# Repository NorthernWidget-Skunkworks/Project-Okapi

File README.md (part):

# Okapi: Data logger with integrated solar charging and modular telemetry

***Okapi data logger (Resnik v0.4.0), with a micro-SD card for local storage and a Particle Boron telemetry module.***

The **Okapi** data logger responds to the need for a robust, flexible, and power-efficient open-source option to record and transmit data from remote locations. It is programmable using the open-source standard Arduino framework via a standard micro-USB cable and supports a wide range of sensor input/output options. It connects to dual power supplies to ensure consistent recordings, and interfaces with a range of “Feather”-form-factor boards for telemetry.

## Namesake

The Okapi, a relative of the giraffe, communicates over long distances using [infrasound](https://en.wikipedia.org/wiki/Infrasound). The telemetry capabilities of this data logger inspired this namesake.

## Technical specifications

### Electronic Hardware

* Microcontroller (computer) core
  * ATMega1284p
  * Arduino compatible
  * Programmable using C++
  * 8 MHz
* Real-time clock
  * DS3231M
  * Temperature-compensated crystal for high accuracy (±5 ppm)
* Sensor and general-purpose connections
  * Primary Rail (selectable 3.3V or 5V)
    * I2C (up to 128 sensors permitted; expansion ports provided by Project Heptapod)
    * SPI
    * 2x 16-bit analog
    * Analog voltage reference
    * 12-bit Digital-to-analog conversion
    * 2x General-purpose input/output
    * USART
    * 2x Vbus (selectable 3.3V or 5V)
    * 2x Ground
  * Secondary Rail (selectable 3.3V or 5V)
    * I2C (up to 128 sensors permitted; expansion ports provided by Project Heptapod)
    * 2x 16-bit analog
    * 2x General-purpose input/output
    * USART
    * 2x Vbus (selectable 3.3V or 5V)
    * 2x Ground
* Data storage and return
  * Local storage: micro SD card
  * Telemetry: support for Feather-profile boards, including Particle devices:
    * Mobile phone networks
    * WiFi
    * Bluetooth
    * [In development] Iridium satellite
* Power
  * Dual power supply
  * Primary Power
    * Built-in maximum-power-point-tracking solar-charge-control circuitry
    * Lithium-Ion battery
  * Backup Power
    * Alkaline AA batteries
  * Real-time clock
    * Coin cell
  * Power consumption
    * Primary power, sleeping: 80 μA
    * Backup power, sleeping: 4 μA
    * Active (typical: data logger without sensors): 10 mA
    * Transmitting (mobile networks, typical: Particle Boron):
      * 16 mA background
      * 40 mA burst
  * Power generation
  * Solar, low light: 100 mA
* User interface
  * “Log” button: instantaneous reading (for testing)
  * “Reset” button
  * 2x 3-color indicator LEDs
  * Computer readout via a serial monitor, included in the Arduino software
* Open-source licensing via CC BY-SA 4.0

>> @bschulz1701: Any updates needed? I think that there is also a WDT (correct?)

### Electronic Software and Firmware

* Programmable using the Arduino IDE https://www.arduino.cc/en/main/software
* Custom bootloader and board definition for ATMega1284p available via https://github.com/NorthernWidget/Arduino_Boards
* Custom libraries from Northern Widget and the open-source community
  * Primary data-logger functions
  * Libraries available with each sensor, exposing a standard interface
* Open-source licensing via GNU GPL 3.0

### Pinout and board interfaces

***Okapi data logger (Resnik v0.4.0) with pins, connectors, and interactive items annotated.***

**Pins are colored following this convention:**
* Ground: black
* Power supply: red
* Universal Serial Asynchronous Receiver--Transmitter (USART or UART): blue
* General-purpose I/O pins: gray
* Analog inputs and associated reference voltage: green
* Digital communications buses (SPI and I2C): purple
* Analog adjustable voltage output: salmon

**The power and programming connectors at the "south" end of the board are as follows:**
* Micro-USB connector
  * The same connector as many Android and other mobile phones at the time of writing; may be programmed using any USB cable for these that is not charging-only (i.e. that can carry data)
  * Can be used with our [clock-setting program](https://github.com/NorthernWidget/SetTime_GUI) to set the time on the real-time clock.
  * Provides power to the data logger while it is connected; this power source is isolated from the batteries and solar panel, and therefore may be plugged in safely at any time.
* Solar panel, 4.95--32.0 V. A wide range of panels can work with this.
* Li-Ion battery, 2.60--4.475 V. This works with standard 18650 Li-ion batteries. It can work well with just a single battery, but if more storage is required, multiple 18650 batteries may be connected in parallel; we have a circuit-board design to do this: https://github.com/NorthernWidget/LiIon-18650-Parallel. ***CAUTION***: most commercially available multiple-18650-battery holders connect them in series; this voltage is ***TOO HIGH*** for the data logger.
* Primary batteries. This is ideally a pack of 3 primary (i.e., not reusable) Alkaline (or better) AA batteries with a long shelf life. The Okapi data logger will switch to these if its rechargeable power supply shuts down. The internal electronics reduce the quiescent power consumption while under backup power (see the above list of [electronic hardware technical specifications](#electronic-hardware)) and inform the logger about which power supply is being used, allowing it to, for example, reduce or temporarily terminate data transmission.

>> @bschulz1701: Solar panel supply current / size?

**"RST" and "LOG" buttons:**
* Reset ("RST"): stop the program that is currently executing on the main logger and return it to its boot sequence.
* Log Now ("LOG"): take a reading immediately. This is useful for diagnoses and testing.

>> General note: we may want to have an LED flash whenever the logger takes a reading -- even for 1/10 of a second. With an option to disable this, of course. But it is often better to know while in the field that a system is working

**Other notes, clockwise from the top:**
* The socket holds a [Feather-form-factor board](https://learn.adafruit.com/adafruit-feather/feather-specification).
  * This standard, designed by [Adafruit](https://www.adafruit.com/), has been widely adopted, including by the IoT/telemetry module designer [Particle](https://www.particle.io/).
  * We often use a [Particle Boron mobile-phone telemetry unit](https://docs.particle.io/boron/).
* Mounting holes for [\#4 screws](https://www.mcmaster.com/91772A106/)
* CR1220 battery; can power the real-time clock for up to 7 years
* ISP header (also called an ICSP header): This 3x2 header is used with an in-system programmer (in-circuit system programmer) to upload the (bootloader)[#installing-the-bootloader] to the data logger.
* A micro-SD card holds a copy of all data, whether or not any telemetry is used

>> @bschulz1701: check my clock 7-year figure

***Okapi data logger (Resnik v0.4.0) with key microchips, LEDs, and switches marked.*** *MCU: Microcontroller. RTC: Real-time clock. LED: Light-emitting diode. Bus: a subsystem for connections and data transfer.*

The Okapi data logger contains two buses (see above), each of which has an independent voltage. The primary bus is on the left and the secondary bus is on the right. These can be selected as 3.3V (switches slid towards the inside of the board) or 5V (switches towards the outside of the board).

>> @bschulz1701: How much power can each bus source/sink?

Two LEDs, status and auxiliary, flash messages to the user to provide information on proper operations vs. a variety of possible errors. These are useful for field diagnoses, and are further described in [the field guide section, below](#field-guide).

>> Design note: move STAT label to left of LED so it can be better seen

The Li-ion override button, which can be pressed with the tip of a pen or other small object, ...

>> @bschulz1701: This somehow overrides the Li-Ion battery electronics to allow something to happen... but I am not remembering what!

## On-board Devices

### I2C

| **Device**                                                        	| **Default address** 	| **Reprogrammable address** 	| **Function**                                                     	|
|-------------------------------------------------------------------	|---------------------	|----------------------------	|------------------------------------------------------------------	|
| [DS3231](https://github.com/NorthernWidget/DS3231_Logger)         	| 0x68                	| N                          	| Real-time clock                                                  	|
| [MCP23018](https://github.com/NorthernWidget-Skunkworks/MCP23018) 	| 0x20                	| N                          	| I/O Expander                                                     	|
| [ADS1115](https://github.com/adafruit/Adafruit_ADS1X15)           	| 0x48                	| N                          	| ADC (on-board devices)                                           	|
| [ADS1115](https://github.com/adafruit/Adafruit_ADS1X15)           	| 0x49                	| N                          	| ADC (off-board devices)                                          	|
| [MCP4725](https://github.com/NorthernWidget-Skunkworks/MCP4725)   	| 0x62                	| N                          	| DAC                                                              	|
| [BME280](https://github.com/NorthernWidget/BME_Library)           	| 0x77                	| N                          	| On-board barometric pressure, temperature, and relative humidity 	|

### SPI

* SD Card

### UART (USART)

* FTDI USB-Serial converter
* Feather form-factor telemetry board; typically [Particle Boron](https://docs.particle.io/boron/)

## Assembly

Assembling this data logger is possible by hand with sufficient skill and the following tools:
* Temperature-controlled soldering iron
* Hot-air rework station
* Equipment for stenciling with solder paste
* ESD-safe tweezers and workstation
* Solder wick

Mechanized assembly by a professional circuit-board assembly house, which is available in many parts of the world, may be preferred due to the complexity of this data logger board.

>> THOUGHT: I have basic instructions for assembly on the [Project Walrus](https://github.com/NorthernWidget-Skunkworks/Project-TPDH-Walrus) README; I will not reproduce these here just yet, as we might want to set up a separate assembly guide, mostly with good links to existing resources, since our writing something of this nature would be to reinvent the wheel.

## Programming

### Downloading and installing the Arduino IDE

Go to https://www.arduino.cc/en/main/software. Choose the proper IDE version for your computer. For Windows, we suggest the non-app version to have more control over Arduino; this might change in the future. You will have to add custom libraries, so the web version will not work (at least, as of the time of writing). Download and install the Arduino IDE. Open it to begin the next steps.

### Installing the bootloader

Before a data logger can receive programs via the convenient USB port, it must have a *bootloader* that tells it to expect to receive new programs that way.  You can read more about bootloaders in general here: https://www.arduino.cc/en/Hacking/Bootloader.

Because you can't upload the bootloader via USB, you use the 2x3-pin 6-pin ICSP (also called ISP) header with a special device called an "in-circuit system programmer" (or just "in-system programmer; yup, that's what the acronym stands for).

Many devices exist to upload a bootloader including:
* The official [AVR ISP mkII](http://ww1.microchip.com/downloads/en/DeviceDoc/Atmel-42093-AVR-ISP-mkII_UserGuide.pdf) (no longer produced but available used)
* Using an [Arduino as an ISP](https://www.arduino.cc/en/tutorial/arduinoISP)
* The versatile [Olimex AVR-ISP-MK2](https://www.olimex.com/Products/AVR/Programmers/AVR-ISP-MK2/open-source-hardware)
* The [Adafruit USBtinyISP](https://www.adafruit.com/product/46)

To upload the bootloader, do the following:

1. Open the Arduino IDE. If you have not yet installed the Northern Widget board definitions, find and install them here (instructions provided): https://github.com/NorthernWidget/Arduino_Boards
2. Select the desired board -- most likely ***ATMega1284p 8MHz*** under *Northern Widget Boards*.
3. Plug the data logger into your computer via a micro-USB cable to provide power.
4. Plug your ISP of choice into your computer (via a USB cable) and onto the 6-pin header. There are two ways to place it on; the header is aligned such that the ribbon cable should be facing away from the board while programming. If this fails without being able to upload, try flipping the header around.
5. Go to Tools --> Programmer and select the appropriate programmer based on what you are using.
6. Go to Tools --> Burn bootloader. Typically, within a few seconds, you learn whether you succeeded or failed. Hopefully it worked!

***Important note for Linux users:*** You must supply permissions to the Arduino IDE for it to be able to use the ICSP, or you will have to run it using `sudo`. The former option is better; the latter is easier in the moment.

***Note: Be sure to download and/or update drivers for your ISP.***

### Installing the requisite software libraries

>> @awickert: Add a full list of the requisite software to install; finish the firmware aggregator and use those directions (or the Arduino ones) to help users install that + sdfat. Include screenshots and host those directions at https://github.com/NorthernWidget-Skunkworks/Firmware-Aggregator.

### How to write a program

The below program is an example that you can copy and paste directly into the Arduino IDE in order to upload to your data logger. We'll walk you through what each piece of the code is and does.

#### Full program
```c++
/*
 * Okapi example: connected with a Walrus pressure--temperature sensor, often
 * used for water-level measurements, via the Longbow I2C/RS-485 translator.
 * Written by Bobby Schulz with a few comments added by Andy Wickert.
 */

#include "Okapi.h"
#include <TP_Downhole_Longbow.h>

TP_Downhole_Longbow Walrus; // Instantiate Walrus sensor; relict library name
Okapi Logger; // Instantiate data logger object

String Header = ""; // Information header; starts as an empty string
uint8_t I2CVals[1] = {0x22}; // I2C addresses of sensors

unsigned long UpdateRate = 60; // Number of seconds between readings

void setup() {
  Header = Header + Walrus.GetHeader();
  Logger.begin(I2CVals, sizeof(I2CVals), Header); // Pass header info to logger
  Init();
}

void loop() {
  Logger.run(Update, UpdateRate);
}

String Update()
{
  Init();
  delay(1500);
  return Walrus.GetString();
}

void Init()
{
  Walrus.begin(13, 0x22); // Instantiate Walrus (at address = 13)
                          // and Longbow Widget (at address = 0x22)
}
```

#### "Include" statements

```c++
#include "Okapi.h"
#include <TP_Downhole_Longbow.h>
```

These bring in the two code libraries involved, the former for the data logger and the latter for the sensors. This allows the user to access the classes and functions within these two libraries, as we will show in more detail below.

#### Instantiate a sensor object

```c++
TP_Downhole_Longbow Walrus; // Instantiate Walrus sensor; relict library name
Okapi Logger; // Instantiate data logger object
```

"Instantiating an object" means that we create our own specific versions of the a class of items. This can be thought of as: `Breakfast myBreakfast`. Breakfast is the general concept, but I create "myBreakfast", which I can then modify. In this same way, "Logger" is what we call our Okapi data logger, and "Walrus" is what we call our "TP_Downhole_Longbow" sensor; this name is a holdover from an earlier design that is the ancestor of the Walrus. We can then access functions and variables within these two instantiated objects.

#### Declare the header string

```c++
String Header = ""; // Information header; starts as an empty string
```

We start with an empty header, but will soon add information to it.

#### Create a list of the I2C addresses of the sensors

```c++
uint8_t I2CVals[1] = {0x22}; // I2C addresses of sensors
```

This is the trickiest step. You need to know what the I2C address of your sensor is. You can skip this, but then the logger will not run a check to see if the sensor is properly connected.

>> Let's make sure that we record this one each page, or find a way to replace this.

#### Declare the amount of time between logging events

```c++
unsigned long UpdateRate = 60; // Number of seconds between readings
```

This is the number of seconds between logging events. If it takes 2 seconds to record data, make sure that you give the logger at least 3 seconds between events. The maximum logging time is set by the watchdog timer, which [FINISH HERE]

>> @BSCHULZ1701: Is there an external WDT on Okapi?

#### `setup()` step: runs once at the start

```c++
void setup() {
  Header = Header + Walrus.GetHeader();
  Logger.begin(I2CVals, sizeof(I2CVals), Header); //Pass header info to logger
  Init();
}
```

`setup()` is a special function that runs just once when the logger boots up. In this case, it first adds the Walrus' header to the header string. `GetHeader()` is a standard function that lies within each of our sensor libraries and returns this header information as a `String`. We then pass the header and the I2C values to the Okapi library's `begin()` function. This sets up the header and prepares the data loger to record data. Finally, this function calls `Init()`, which we skip ahead to describe immediately below.

>> (awickert): I still don't understand why we have to pass `sizeof()` and can't just compute that within the function.

#### `Init()` function: skipping ahead to understand `setup()`

```c++
void Init()
{
  Walrus.begin(13, 0x22); // Instantiate Walrus (at address = 13)
                          // and Longbow Widget (at address = 0x22)
}
```

The `Init()` function calls the `begin()` function, standard within each Northern Widget sensor library, to instantiate the connection ports (e.g., I2C, RS-485) used to communicate between the sensor and the logger. In this case, there is only one sensor, but two ports are needed: An RS-485 signal goes from the Walrus to the Longbow Widget, which then converts the signal into an I2C signal with its own address. The reason for this is that an I2C signal can travel only ~3 m, but an RS-485 signal can travel ~100 m.

#### `loop()` step: keeps running until stopped

```c++
void loop() {
  Logger.run(Update, UpdateRate);
}
```

The loop calls the main function of the Okapi library, `run()`, repeatedly. This puts the logger into a low-power sleep mode and wakes it up only when interrupted by the clock or the "LOG" button. `Update` refers to the function described immediately below. `UpdateRate` is our logging interval defined above.

#### `Update()` function: Gives data for the logger to record

```c++
String Update()
{
  Init();
  delay(1500);
  return Walrus.GetString();
}
```

The `Update()` function first calls the `Init()` function to be sure that the sensor is ready to log. It then in this case delays 1500 milliseconds; this is an ad-hoc solution to the question of how long it takes the pressure transducer to settle after being started up, and is a safe large amount of time. This function then can `return` a string of all of the Walrus' readings (one pressure and two temperature measurements) separated by commas. This is then concatenated to a list of logger-internal measurements -- date/time; on-board temperature, pressure, and relative humidity; and onboard voltages for battery and solar-panel status -- and recorded to the SD card. If telemetry were present, these data could also be sent to a remote location.

### Reference

A full index of the public variables and functions within the Okapi data logger library is available at https://github.com/NorthernWidget/Okapi_Library.

>> Send user to library page

>> Thoughts: We should make all comments compatible with doxygen (following) what I did with the ALog library. It also looks like TravisCI has support for Arduino(!) This means that we could also automate construction of the documentation for these libraries.

### Integration with Particle Boron

>> @bschulz1701?

## Wiring

>> Example needed

## Power supply

* **Lithium-ion 18650 rechargeable batteries**; this board can hold two in parallel: https://github.com/NorthernWidget/LiIon-18650-Parallel
* **Solar panel**. A wide range is acceptable, but we like [Voltaic Systems' 6-watt panel](https://voltaicsystems.com/6-watt-panel/). If you do not want to snip off the barrel jack, [this extension plug from Adafruit should work](https://www.adafruit.com/product/2788) (though we have not tested it... and you'll also have to cut *it* in half).
* **Primary alkaline batteries**; we typically use three high-quality (e.g., Duracell) AAs. These are the backup power supply, and we place them in a [3xAA holder (in series for the proper voltage) with a switch](https://www.jameco.com/z/SBH-331-AS-R-3x-AA-Battery-Holder-with-Cover-and-Switch_216144.html).

>> @bschulz1701: new smarter 18650 holder?

## Housing

The below suggestions encompass what we use and suggest for the housing. In the end, any sufficiently waterproof enclosure will work.

### Materials

* **Enclosure**: [PolyCase WH-16-03 outdoor-rated hinged enclosure](https://www.polycase.com/wh-16)
* **Cable glands**: [RDC07AA](https://www.elecdirect.com/catalogsearch/result/?q=RDC07AA). One per sensor, plus one for the solar panel.
>> AW: Photo didn't take; look up
* **Fasteners**
  * [M5-0.8 x 10 mm truss head screws](https://www.mcmaster.com/92467A320/) x4 to attach mounting plate to threaded inserts in the enclosure
  * [\#4-40 x 1/4 in pan head screws](https://www.mcmaster.com/91772A106/) x22 to attach Okapi, battery packs, and mounting plate to standoffs
  * [\#4-40 x 2 in Female Threaded Hex Standoffs](https://www.mcmaster.com/91115A173/) x3 to stand off Okapi from mounting plate
  * [\#4-40 x 1/2 in Female Threaded Hex Standoffs](https://www.mcmaster.com/91920A533/) x8 to stand off AA battery pack and Li-Ion battery pack from mounting plate
* **Mounting plate for Okapi** (Milled, ABS)
  * [Mounting Plate Design](Mounting%20Plate)
* **Power**
>> Solar panel
  * [3x AA battery pack BK-1280-PC6](https://www.digikey.com/en/products/detail/mpd-memory-protection-devices/BK-1280-PC6/1640076) for alkaline battery backup, mounting holes included for #4-40 screws
>> Li-Ion battery and holder

### Tools

* CNC mill and/or drill press
* Deburring tool or knife + skill and patience
* Torque wrench(es) for 1.0, 1.2 N m

### Assembly

>> Guide with photos. Perhaps ask @superchap123 to use his CNC

>> Placeholder for Now

>> Also include information on passing wiring through

## Field operator's guide

### Initialize
1. Ensure that all connections are secure and SD card is inserted
2. Turn battery pack on
3. Wait for GREEN - GREEN - 5x Blue Flash
	- If you see this, the logger is properly recording data. To double-check, go to "Check"
	- If you see a different flash pattern, go to "Error"

### Check
1. After going through "Initialize", wait 2-3 minutes
2. Follow the instructions in the "Download" section
3. Check to make sure that all the data are being recorded at the proper (UTC) time
4. Check that valid values are being recorded for sensors
7. Whether or not files are properly recorded, return to "Initialize"
	- If files are not recorded, replace the SD card, check all connections, turn the logger back
	  on, and try again
	- If there is an issue with a specific sensor, check connections and troubleshoot
	- If files are recorded properly, return to Initilaize and do not return to "Check"

### SD card swap
1. Turn battery pack off
2. Remove SD card. Ensure that it is labeled. Put it somewhere safe and memorable
3. Replace the SD card with an equivalently labeled SD card
4. Go to "Initialize"

### Download
1. Turn battery pack off
2. Remove SD card
3. Insert SD card in computer
4. Navigate in the SD card to the most recent "log" file (NW→<serial_number>→Log<number>.txt)
5. Save the data file in a well-labeled and organized place.
6. Safely eject the SD card from the computer
7. Go to "Initialize"

### Error

#### Status Codes

The first LED (AUX) will turn green so long as power is applied.
The second LED (STAT) will have one of the colors below.

**Green:**: All systems check out OK, logging will proceed

**Orange:**: A sensor system is not registering properly, some sensor data may be missing or incorrect
* Verify correct polarity of sensor connection
* Ensure the right sensor is connected
* Verify the screw terminals are well connected to the wires (a loose connection can cause a failure)
* Make sure battery power is applied, some sensors can fail otherwise

**Cyan:**: Clock time is incorrect, but logger is otherwise working correctly
* Connect the logger to a computer and reset the clock using the Northern Widget Time Set GUI
* Start Processing
* Open the Northern Widget Time Set program
* Note and record the wrong time if the logger has been out in the field, alongside the current (correct) time, to correct the prior measurements
* Click the "set time" button and check that you are <3 seconds off of the correct time
* Click the "close" button

**Pink**: (looks like purple to some people): SD card is not inserted
* Insert the SD card, or remove and re-insert to make sure card is fully seated

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
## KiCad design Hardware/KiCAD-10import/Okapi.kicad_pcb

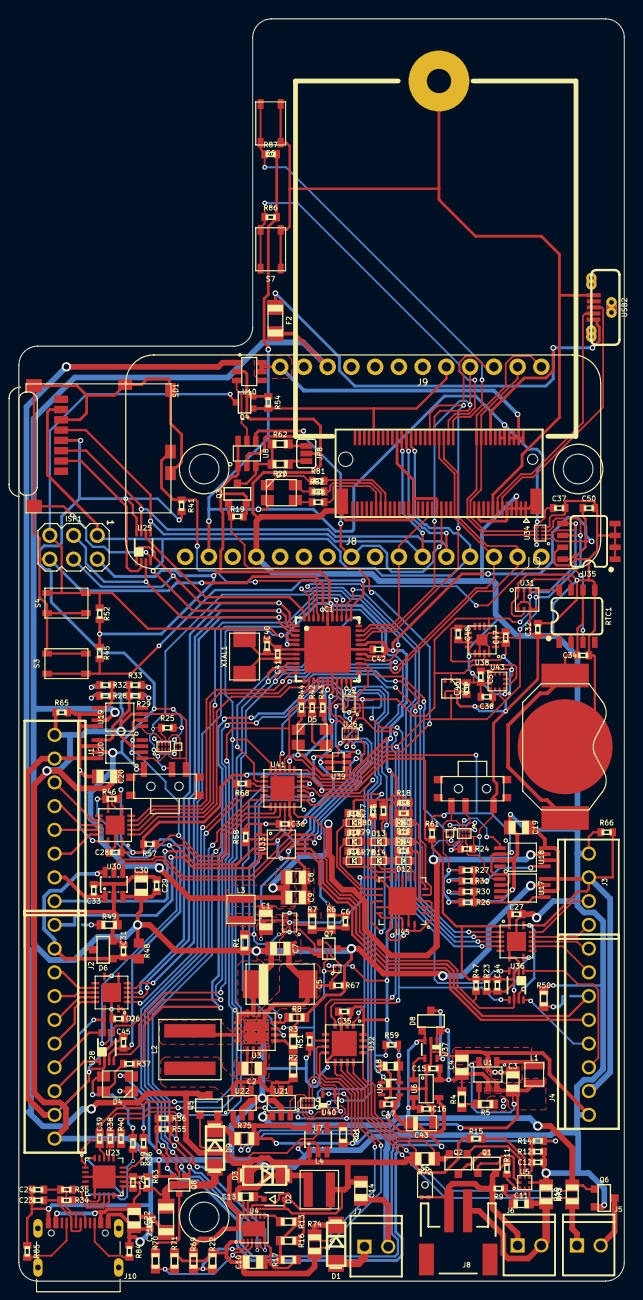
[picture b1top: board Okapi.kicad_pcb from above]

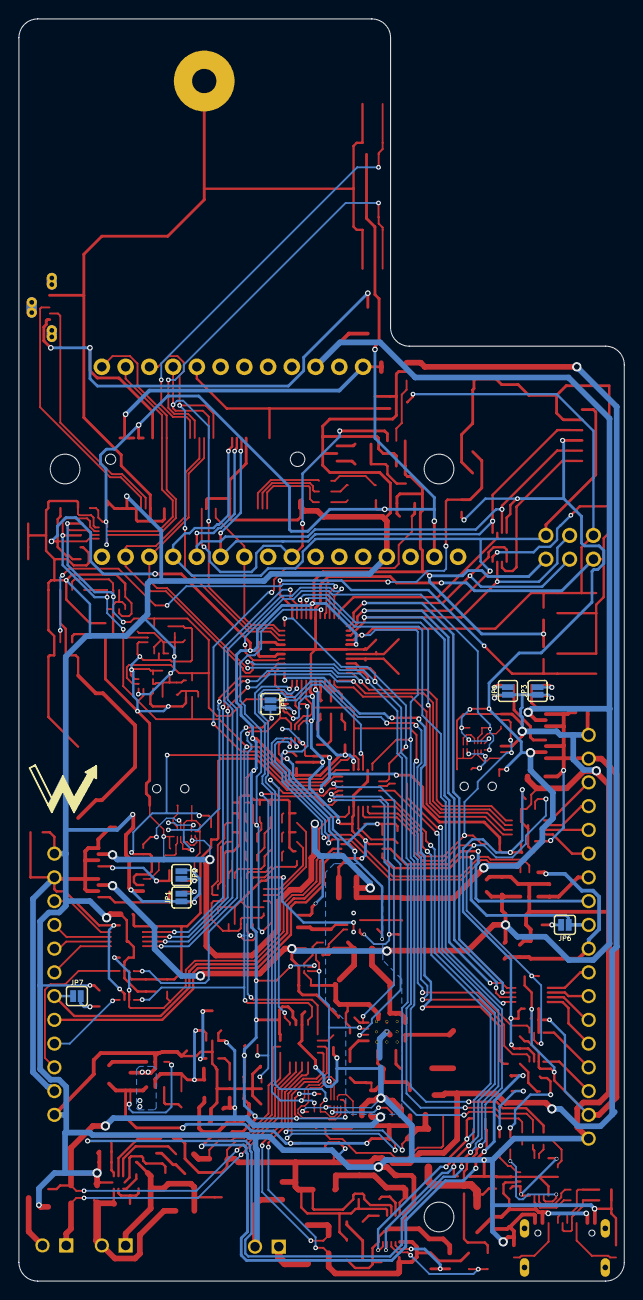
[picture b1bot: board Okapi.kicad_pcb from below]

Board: 2 copper layers, 64.8 x 135.0 mm, 252 parts (8 on the bottom side), 207 nets.

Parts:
BT1: BATTERY_COIN12MM; LINX_BAT-HLD-012-SMT
C1: 4.7uF; C0805
C2, C7, C8, C9, C10, C19, C20: 22uF; C0805
C3, C4, C14, C22, C30: 10uF; C0805
C5: 220uF; C2917
C6: 68pF; C0402
C11, C13: 1uF; C0603
C12, C17, C21, C25, C26, C27, C28, C29, C31, C32, C33, C34, C35, C36, C37, C38, C39, C44, C45, C46, C47, C48, C50, C57: 0.1uF; C0402
C15, C16: 0.22uF; C0402
C18: 4.7uF; C0603
C23, C24, C40, C41: 12pF; C0402
C42: 1uF; C0402
C43: 100uF; C1206_TANT
D1, D3, D9: DO214AC
D2: SOD323-R
D4, D5, D7: CLVBA-FKA
D6: SOT23-3
D8: BAT54C; SOT23-3@1
D10, D13, D16: LEDGREEN0603; LED_0603
D11, D14, D17: LEDYELLOW0603; LED_0603
D12, D18: LEDRED0603; LED_0603
F1, F2: 1206
H1, H2, H3: 4_40
IC1: ATMEGA1284M; MLF44-TH
ISP1: AVRISP-6; AVRISP
J1, J4: CONN_82.54_SCREW; 1X08_SCREW
J2: 1X10_SCREW
J3: CONN_42.54_SCREW; 1X04_SCREW
J5, J6, J7: 1X02_2.54_SCREWTERM
J8: JST-2-SMD
J9: B_SERIES_M.2EKEY_NOPROG; PARTICLE_M.2EKEY_NOPROG
J10: USB_C_CUSB31-CFM2AX-01-X
JP1, JP2, JP3, JP4, JP5, JP6, JP7: JUMPER-SMT_2_NO_SILK; SMT-JUMPER_2_NO_SILK_528
JP8: JUMPER-SMT_3_1-NC_PASTE_SILK; SMT-JUMPER_3_1-NC_PASTE_SILK_528
L1: 6.8uH; 1008
L2: 10uH; WE-XHMI(6.65X6.45)
L3: 1uH; WE-LQS(3X3)
L4: 4.7uH; WE-MAIA(4.1X4.1)
MS1: FEATHERWINGLAYOUT; FEATHERWING_MIN
Q1, Q2, Q6: DMG3404; SOT23-3
Q3, Q5: FDN360P; SOT23-3@1
Q4, Q7, Q8: 2N7002; SOT323
R1, R5, R7, R8: 180k; R0603
R2, R4: 1.62M; R0603
R3: 360k; R0603
R6: 820k; R0603
R9, R36, R37, R38, R39, R40, R42, R43, R44: 330; R0402
R10: 3m; R0805
R11: 20; R0402
R12: 1k; R0402
R13: 182k; R0603
R14: 100R; R0402
R15: 2k; R0402
R16: 91k; R0603
R17, R62: 330k; R0603
R18, R23, R57, R58, R61, R63: 100k; R0402
R19: 120k; R0402
R20: 130k; R0603
R21: 470k; R0603
R22: 143k; R0603
R24, R25, R41, R45, R46, R47, R52, R67: 10k; R0402
R26, R27, R28, R29, R30, R31, R32, R33: 287R; R0402
R34, R35: 27; R0402
R48: 330R; R0603
R49, R50: 10k; R0603
R51, R54, R84, R85, R86, R87: R0402
R53, R60, R64, R76, R77, R78, R79, R80: 220R; R0402
R55, R56, R59, R68: 1M; R0402
R65, R66: 180k; R0402
R69: 100k; R0603
R70: 200k; R0603
R71: 1M; R0603
R72, R73, R74, R75: R0805
R81, R82, R83: 5.6k; R0402
RTC1: DS3231M; SO08
S1, S2: SPDTPCM12; PCM12
S3, S4, S6, S7: BUTTON4.2X3.2; SWITCH_4.2X3.2
S5: BUTTON2.6X1.6; SWITCH_2.6X1.6
SD1: MICROSDCD; MICROSD_CD
U1: TLV61220DBV; DBV_R-PDSO-G6
U2: TPS62822DLC; DLC_8
U3: TPS61032RSA; RSA_S-PVQFN-N16
U4: DFN_12_3X3
U5: BQ2980RUG; RUG_S-PQFP-N8
U6: TPS2105; SOT23-5
U7: LTC4412S6; SOT23-6L
U8: TPL5111DDC; DDC_R-PDSO-G6
U9: TPS79733; DCK_R-PDSO-G5
U10, U21, U22: TPS22917DBV; DBV_R-PDSO-G6
U11, U12, U13: SN74AUP1G04YFP; DSBGD_4
U14, U15, U16: SN74AUP2G08DQE; DQE_R-PX2SON-N8
U17, U18, U19, U20: MIC2544MSOP; MSOP_8
U23: FT231X-Q; QFN20
U24: SN74LVC1G3157DRL; DRL_R-PDSO-N6
U25: SN74AUP3G34DCU; DCU_(R-PDSO-G8)
U26, U34: TXS0102DQM; DQM_R-PX2SON-N8
U27, U29, U42: TXS0104RGY; RGY_S-PVQFN-N14
U28, U36: TCA9406DCU; DCU_(R-PDSO-G8)
U30: MCP4726A2SOT-23; SOT23-6L
U31: BME280
U32: PAC1934QFN; QFN16
U33: ADS1115; VSSOP_10
U35: MB85RC; SO08
U37: TLV3691DCK; DCK_R-PDSO-G5
U38: MLX90393; QFN16_3X3
U39: MIC94094C6; SC-70_6
U40: SN74AHC1G86DCK; DCK_R-PDSO-G5
U41: MCP23018QFN; QFN24
U43: BMA456; LGA-12_2X2
U44: VEML6030
U45: PCA9634QFN; QFN20_5X5
U$1, U$2: VDIV-JP; VDIV_GENERIC
U$4: NWLOGO_MED
USB2: USB_MICROVERT; USB_MICRO_VERT_MOLEX
XTAL1: CRYSTAL8MHZ5X3.2; CRYSTAL_5X3.2_2-SMD

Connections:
3V3_AUX: C6.1, C8.1, C9.1, C32.1, C38.1, C46.1, C47.1, C48.1, C57.1, L3.P$2, R6.2, R24.2, R25.2, R41.2, RTC1.2, S1.1, S2.1, SD1.4, U11.A2, U12.A2, U14.8, U15.8, U18.7, U20.7, U24.5, U25.8, U31.2, U31.5, U31.6, U31.8, U38.2, U38.8, U38.15, U39.6, U43.3, U43.7, U43.10, U44.4, U44.6
3V3_AUX_PG: R1.1, U2.8, U41.2
3V3_CORE: C18.1, C35.1, C42.1, C50.1, D4.2, D5.2, IC1.5, IC1.17, IC1.27, IC1.29, IC1.38, ISP1.2, Q3.2, R18.2, R19.2, R45.2, R52.2, R53.2, R55.2, R56.2, R59.2, R60.2, R64.2, R76.2, R77.2, R78.2, R79.2, R80.2, U8.1, U8.6, U9.5, U13.A2, U16.8, U32.2, U32.15, U32.16, U34.1, U35.8, U39.4, U40.5, U41.8, U45.3, U45.15, U45.18, U45.20
3V3_CORE_ISO: C26.1, C27.1, C28.1, C44.1, C45.1, R23.2, R46.2, R47.2, R57.2, R61.2, U26.1, U26.5, U27.1, U28.3, U29.1, U36.3, U39.1, U42.1
3V3_FEATHER: C37.1, D7.2, J9.10, J9.12, MS1.2, R86.2, R87.2, U34.5, U34.8
3V3_FTDI: C25.1, U23.10, U23.11, U23.20
5V_AUX: C1.1, C5.+, C7.1, C29.1, C30.1, C36.1, F2.2, MS1.26, Q7.3, R1.2, R8.2, R48.2, R58.2, R67.2, U2.7, U3.1, U3.15, U3.16, U17.7, U19.7, U26.8, U30.3, U33.1, U33.8
5V_LP: C4.1, C15.1, D8.2, R4.2, U1.5, U6.5, U37.1
ADC_0: J1.8, U33.4
ADC_1: J2.1, JP6.1, U33.5
ADC_2: J4.5, U33.6
ADC_3: J4.6, JP7.1, U33.7
ADC_EXT_ALERT: R58.1, U33.2, U41.22
ALIVE_LED: IC1.23, R37.2
BLUE: J9.65, R83.2
BMS_CTR: R14.1, U41.16
BSOM_VUSB: F2.1, J9.16, USB2.1
BUS_LOGIC_EN_PRIME: R46.1, U27.8, U28.6, U29.8, U41.21
BUS_LOGIC_EN_SEC: R47.1, U36.6, U41.24, U42.8
C0: IC1.21, U16.2, U40.1
C1: IC1.22, U16.6, U40.2
CC1: J10.A5, R85.2
CC2: J10.B5, R84.2
CSA_~ALERT: U32.1, U41.4
CS_EXT: IC1.37, U27.2
CS_OUT: J2.6, U27.13
D+: C24.2, J10.A6, J10.B6, R35.2
D-: C23.2, J10.A7, J10.B7, R34.2
DAC_OUT: C33.1, J1.7, U30.1
DTR: C39.1, U23.18
EN_BUS_PRIME: IC1.26, R25.1, U15.1, U15.6
EN_BUS_SEC: IC1.25, R24.1, U14.1, U14.6
FAULT_PRIME: R57.1, U19.2, U20.2, U41.20
FAULT_SEC: R61.1, U17.2, U18.2, U41.6
FEATHER_BAT: J9.2, J9.4, J9.6, J9.8, MS1.28, U10.5, U10.6
FEATHER_CTS: IC1.31, J9.40, MS1.20
FEATHER_EN: Q3.1, R19.1, U41.7
FEATHER_GPIO: IC1.32, J9.43, MS1.10
FEATHER_RTS: IC1.30, J9.42, MS1.19
GLOBAL_INT: IC1.33, U41.14
GND: BT1.GND, C1.2, C2.2, C3.2, C4.2, C5.-, C7.2, C8.2, C9.2, C10.2, C12.2, C14.2, C15.2, C16.2, C17.2, C18.2, C19.2, C20.2, C21.2, C22.2, C23.1, C24.1, C25.2, C26.2, C27.2, C28.2, C29.2, C30.2, C31.2, C32.2, C33.2, C34.2, C35.2, C36.2, C37.2, C38.2, C40.1, C41.1, C42.2, C43.-, C44.2, C45.2, C46.2, C47.2, C48.2, C50.2, C57.2, D3.A, D6.2, IC1.6, IC1.18, IC1.28, IC1.39, IC1.TH, ISP1.6, J1.1, J2.10, J3.1, J4.1, J7.P1, J9.1, J9.3, J9.5, J9.7, J9.9, J9.15, J9.21, J9.39, J9.49, J9.56, J9.76, J9.77, J9.GND, J10.A1B12, J10.B1A12, JP1.1, JP2.1, JP3.1, JP4.1, JP8.2, MS1.4, Q4.2, Q6.2, Q7.2, Q8.2, R3.1, R5.1, R7.1, R10.2, R12.1, R17.2, R23.1, R26.1, R27.2, R28.1, R29.2, R49.1, R50.1, R51.1, R54.1, R63.1, R65.1, R66.1, R67.1, R69.1, R84.1, R85.1, RTC1.5, S1.3, S2.3, S3.1, S3.2, S4.1, S4.2, S6.3, S6.4, S7.3, S7.4, SD1.6, SD1.CD2, SD1.MT1, SD1.MT2, SD1.MT3, SD1.MT4, U1.2, U2.3, U2.5, U3.5, U3.6, U3.7, U3.13, U3.PAD, U3.PAD@1, U3.PAD@2, U3.PAD@3, U3.PAD@4, U3.PAD@5, U3.PAD@6, U3.PAD@7, U3.PAD@8, U3.PAD@9, U4.6, U4.EP, U5.4, U6.2, U7.2, U7.3, U8.2, U9.2, U10.2, U11.B1, U12.B1, U13.B1, U14.4, U15.4, U16.4, U17.3, U18.3, U19.3, U20.3, U21.2, U22.2, U23.3, U23.6, U23.13, U23.EP, U24.2, U25.4, U26.4, U27.7, U27.EP, U28.2, U29.7, U29.EP, U30.2, U31.1, U31.7, U32.3, U32.EP, U33.3, U34.4, U35.1, U35.2, U35.3, U35.4, U35.7, U36.2, U37.2, U38.4, U38.9, U38.10, U38.11, U38.12, U38.13, U38.14, U38.16, U38.EP, U39.2, U39.5, U40.3, U41.11, U41.23, U41.EP, U42.7, U42.EP, U43.1, U43.8, U43.9, U44.1, U45.1, U45.2, U45.8, U45.14, U45.19, U45.EP, USB2.5
GPIO_0: IC1.13, U29.2
GPIO_0_OUT: J1.6, U29.13
GPIO_1: IC1.36, U29.3
GPIO_1_OUT: J1.5, U29.12
GPIO_2: IC1.43, U42.5
GPIO_2_OUT: J4.7, U42.10
GPIO_3: IC1.35, U42.4
GPIO_3_OUT: J4.8, U42.11
GREEN: J9.63, R82.2
LBI: R8.1, U3.12, U41.3
LED1: IC1.14, R44.1
LED2: IC1.15, R42.1
LED3: IC1.16, R43.1
LI+: J6.P2, J8.2, Q1.2, R9.2, R11.2, S5.A, S5.A'
LI-: C11.2, J6.P1, J8.1, R10.1, U5.3
LOG_INT: IC1.34, R45.1, S3.3, S3.4
MISO: IC1.2, ISP1.1, J9.50, MS1.13, SD1.7, U27.3
MISO_OUT: J2.5, U27.12
MOSI: IC1.1, ISP1.4, U25.1, U27.4
MOSI_BUF: J9.52, MS1.12, SD1.3, U25.7
MOSI_OUT: J2.4, U27.11
MPPT_CHRG: Q8.1, R55.1, U4.4, U41.18
MPPT_FAULT: R56.1, U4.5, U41.19
MPPT_SHDN: R70.2, R71.1, U4.3
MPPT_VIN_REG: R22.1, R69.2, U4.2
unnamed: L3.P$1, U2.6
unnamed: C6.2, R6.1, R7.2, U2.2
unnamed: R2.1, R3.2, U3.9
unnamed: L2.2, U3.3, U3.4
unnamed: Q1.3, Q2.3
unnamed: R4.1, R5.2, U1.4
unnamed: Q1.1, U5.8
unnamed: L1.2, U1.1
unnamed: Q2.1, U5.7
unnamed: R15.2, U5.6
unnamed: R13.1, R16.2, R17.1
unnamed: C12.1, R12.2, R14.2, U5.5
unnamed: R11.1, U5.1
unnamed: R13.2, U4.7
unnamed: C11.1, R9.1, U5.2
unnamed: R68.1, U41.15
unnamed: C13.2, D2.C, U4.11
unnamed: JP8.3, R20.1
unnamed: C13.1, D3.C, L4.P$1, U4.12
unnamed: R51.2, U32.6
unnamed: Q8.3, R70.1
unnamed: U16.7, U21.3
unnamed: U16.3, U22.3
unnamed: D10.CATHODE, U45.4
unnamed: U12.B2, U15.5
unnamed: R28.2, R32.2, U19.5
unnamed: S2.2, U12.A1, U15.2
unnamed: U15.7, U19.1
unnamed: U15.3, U20.1
unnamed: JP3.2, R32.1
unnamed: JP4.2, R33.2
unnamed: R29.1, R33.1, U20.5
unnamed: U11.B2, U14.5
unnamed: S1.2, U11.A1, U14.2
unnamed: U14.7, U17.1
unnamed: U14.3, U18.1
unnamed: R26.2, R30.2, U17.5
unnamed: JP1.2, R30.1
unnamed: JP2.2, R31.2
unnamed: R27.1, R31.1, U18.5
unnamed: JP8.1, R62.1
unnamed: BT1.POWER0, BT1.POWER1, C34.1, RTC1.6
unnamed: R38.2, U23.17
unnamed: Q5.1, U7.5
unnamed: R21.1, U7.4
unnamed: R40.2, U23.1
unnamed: R35.1, U23.8
unnamed: R39.2, U23.14
unnamed: R34.1, U23.9
unnamed: D4.1, R39.1
unnamed: D4.3, R36.1
unnamed: D4.4, R37.1
unnamed: R36.2, U23.7
unnamed: D5.3, R42.2
unnamed: D5.4, R43.2
unnamed: D5.1, R44.2
unnamed: C40.2, IC1.7, XTAL1.OSC2
unnamed: C41.2, IC1.8, XTAL1.OSC1
unnamed: Q3.3, R20.2, R62.2, U8.3
unnamed: U8.5, U10.3
unnamed: JP6.2, R49.2
unnamed: JP7.2, R50.2
unnamed: D11.CATHODE, U45.5
unnamed: Q7.1, U13.B2
unnamed: D8.3, U37.5
unnamed: D12.CATHODE, U45.6
unnamed: D13.CATHODE, U45.7
unnamed: D14.CATHODE, U45.9
unnamed: D16.CATHODE, U45.10
unnamed: D17.CATHODE, U45.11
unnamed: D18.CATHODE, U45.12
unnamed: D10.ANODE, R53.1
unnamed: D11.ANODE, R60.1
unnamed: D12.ANODE, R64.1
unnamed: D13.ANODE, R76.1
unnamed: D14.ANODE, R77.1
unnamed: D16.ANODE, R78.1
unnamed: D17.ANODE, R79.1
unnamed: D18.ANODE, R80.1
unnamed: D7.1, R81.1
unnamed: D7.4, R82.1
unnamed: D7.3, R83.1
PD+: J9.11, USB2.3
PD-: J9.13, USB2.2
PG_LDO: R59.1, U9.1, U41.1
POWER_EN: U2.1, U3.11, U13.A1, U16.1, U16.5, U40.4
QOD: U21.5, U22.5
RED: J9.61, R81.2
RST: C39.2, IC1.4, ISP1.5, Q4.3, R52.1, S4.3, S4.4, U41.12
RST_TRIG: J9.66, MS1.21, Q4.1, R54.2
RTC_INT: IC1.42, RTC1.3
RX: IC1.9, J9.36, MS1.15, R38.1
RX_EXT: IC1.11, U29.5, U42.2
RX_OUT_PRIME: J1.3, U29.10
RX_OUT_SEC: J3.3, U42.13
SCK: IC1.3, ISP1.3, U25.3, U27.5
SCK_BUF: J9.54, MS1.11, SD1.5, U25.5
SCK_OUT: J2.3, U27.10
SCL: IC1.19, RTC1.8, U26.3, U28.5, U31.4, U32.4, U34.3, U35.6, U36.5, U38.3, U41.9, U43.12, U44.5, U45.16
SCL_5V: U26.6, U30.5, U33.10
SCL_FEATHER: J9.20, MS1.18, U34.6
SCL_OUT_PRIME: J2.7, U28.8
SCL_OUT_SEC: J4.4, U36.8
SDA: IC1.20, U24.4
SDA_5V: U26.7, U30.4, U33.9
SDA_CTRL: IC1.24, U24.6
SDA_EXT: JP5.2, U24.1, U28.4, U36.4
SDA_FEATHER: J9.22, MS1.17, U34.7
SDA_OB: JP5.1, RTC1.7, U24.3, U26.2, U31.3, U32.5, U34.2, U35.5, U38.5, U41.10, U43.2, U44.2, U45.17
SDA_OUT_PRIME: J2.8, U28.1
SDA_OUT_SEC: J4.3, U36.1
SD_CD: IC1.41, R41.1, SD1.CD1
SD_CS: IC1.44, U25.6
SD_CS_BUF: SD1.2, U25.2
TX: IC1.10, J9.38, MS1.14, R40.1
TX_EXT: IC1.12, U29.4, U42.3
TX_OUT_PRIME: J1.4, U29.11
TX_OUT_SEC: J3.4, U42.12
VBUS_PRIME: C20.1, J1.2, J2.9, R65.2, U19.6, U19.8, U20.6, U20.8, U27.14, U28.7, U29.14
VBUS_SEC: C19.1, J3.2, J4.2, R66.2, U17.6, U17.8, U18.6, U18.8, U36.7, U42.14
VREF: C31.1, D6.1, J2.2, R48.1, U30.6
VUSB: C21.1, C22.1, F1.1, J10.A4B9, J10.B4A9, U23.12
VUSB_POWER: D9.A, F1.2, R63.2, R68.2
V_BETA: C3.1, L1.1, R21.2, R75.2, U1.3, U1.6, U7.6, U22.1, U32.7
V_BETA_SENSE: D9.C, Q5.2, R75.1, U32.8
V_CORE: C17.1, C43.+, U6.4, U9.4
V_CORE_SW: U6.1, U37.4
V_HP: C2.1, L2.1, R2.2, U3.8, U21.6, U22.6
V_HP_SYNC: U3.10, U41.5
V_LI: C14.1, D2.A, L4.P$2, Q5.3, R15.1, R16.1, R72.2, S5.B, S5.B', U4.9, U4.10, U7.1, U10.1, U32.13
V_LI_SENSE: Q2.2, R72.1, U32.14
V_PRIME: C16.1, D8.1, Q6.1, R73.2, U6.3, U21.1, U32.12, U37.3
V_PRIME-: J5.P1, Q6.3
V_PRIME_SENSE: J5.P2, R73.1, U32.11
V_SOLAR: D1.A, J7.P2
V_SOLAR_IN: C10.1, R22.2, R71.2, R74.2, U4.1, U32.9
V_SOLAR_SENSE: D1.C, R74.1, U32.10
WD_DONE: J9.37, MS1.8, U8.4
~LED_EN: IC1.40, R18.1, U45.13
~MODE: J9.32, R87.1, S6.1, S6.2
~RST: J9.34, R86.1, S7.1, S7.2

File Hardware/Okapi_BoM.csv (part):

Qty,Value,Device,Package,Parts,Description,DIGIKEY,DISP,MF,MFP,MOUSER,MPN,PROD_ID,VALUE,VALUE_PART
3,,CONN_022.54_SCREW,1X02_2.54_SCREWTERM,"J5, J6, J7",Genaric 2 terminal header,ED10561-ND,,OnShore,,,OSTVN02A150,,,
1,,CONN_102.54_SCREW,1X10_SCREW,J2,Genaric 10 terminal header,ED10567-ND,,On Shore,,,OSTVN10A150,,,
1,,DIODEDO-214AC,DO214AC,D9,Genaric Diode,B340A-FDICT-ND,,Diodes Incorporated,,,B340A-13-F,,,
2,,DIODEDO-214AC,DO214AC,"D1, D3",Genaric Diode,CMSH3-40MATR13CT-ND,,Central Semiconductor,,,CMSH3-40MA TR13,,,
1,,DIODESOD-323,SOD323-R,D2,Genaric Diode,CMDSH2-3CT-ND,,Central Semiconductor,,,CMDSH2-3 TR,,,
1,,JST_2MM_MALE,JST-2-SMD,J8,JST 2MM MALE RA CONNECTOR,455-1749-1-ND,,JST,,,S2B-PH-SM4-TB(LF)(SN),,,
2,,LM40402.5,SOT23-3,"D6, D7",LM4040 - Precision Micropower Shunt Voltage Referance,576-1047-1-ND,,Microchip,,,LM4040DYM3-2.5-TR,,,
1,,LT3652DD,DFN_12_3X3,U4,LT3652 - Power Tracking Battery Charger for Solar Power (MPPT),LT3652EDD#PBF-ND,,LT,,,LT3652EDD#PBF,,,
3,,MOUNTING_HOLE4_NP,4_40,"H1, H2, H3",Genaric Mechanical Mounting Hole,,,,,,,,,
1,,R-EU_10KR0402,R0402,R54,"RESISTOR, European symbol",311-10.0KHRCT-ND,,Yageo,,,RC0603FR-0710KL,,,10k
19,0.1uF,C-EU0.1UFC0402,C0402,"C12, C17, C21, C25, C26, C27, C28, C29, C31, C32, C33, C34, C35, C36, C37, C38, C39, C44, C45","CAPACITOR, European symbol",490-4759-1-ND,,Murata,,,GCM155R71C104KA55D,,,
2,0.22uF,C-EU0.22UFC0402,C0402,"C15, C16","CAPACITOR, European symbol",490-12265-1-ND,,Murata,,,GRT155R61E224KE01D,,,
2,1.62M,R-EU_1.62MR0603,R0603,"R2, R4","RESISTOR, European symbol",RMCF0603FT1M62CT-ND,,Stackpole,,,RMCF0603FT1M62,,,1.62M
1,100R,R-EU_100R0402,R0402,R14,"RESISTOR, European symbol",311-100LRCT-ND,,Yageo,,,RC0402FR-07100RL,,,100
6,100k,R-EU_100KR0402,R0402,"R23, R57, R58, R60, R61, R63","RESISTOR, European symbol",311-100KLRCT-ND,,Yageo,,,RC0402FR-07100KL,,,100k
1,100k,R-EU_100KR0603,R0603,R69,"RESISTOR, European symbol",RC0402FR-071ML,,Yageo,,,RC0603FR-07100KL,,,100k
1,100uF,CTANT_EU1206,C1206_TANT,C43,Genaric Tantalum Capacitor,718-1921-1-ND,,Vishay Sprague,,,TL8A0107M010D,,,
8,10k,R-EU_10KR0402,R0402,"R24, R25, R41, R45, R46, R47, R52, R67","RESISTOR, European symbol",311-10.0KHRCT-ND,,Yageo,,,RC0603FR-0710KL,,,10k
2,10k,R-EU_P10KR0603,R0603,"R49, R50","RESISTOR, European symbol",P10KDBCT-ND,,Panasonic,,,ERA-3AEB103V,,,10k
5,10uF,C-EU10UFC0805,C0805,"C3, C4, C14, C22, C30","CAPACITOR, European symbol",490-6473-6-ND,,Murata,,,GRM21BR61C106KE15K,,,
1,10uH,INDUCTORXHMI_6.65X6.45,WE-XHMI(6.65X6.45),L2,Genaric inductor,732-10707-1-ND,,Wurth,,,74439346100,,,
1,120k,R-EU_120KR0402,R0402,R19,"RESISTOR, European symbol",311-120KLRCT-ND,,Yageo,,,RC0402FR-07120KL,,,120k
2,12pF,C-EU12PFC0402,C0402,"C23, C24","CAPACITOR, European symbol",445-5585-1-ND,,TDK,,,CGA2B2C0G1H120J050BA,,,
2,12pF,C-EU12PFC0402,C0402,"C40, C41","CAPACITOR, European symbol",1276-1254-1-ND,,Samsung,,,CL10C120JB8NNNC,,,
1,130k,R-EU_130KR0603,R0603,R20,"RESISTOR, European symbol",311-130KHRCT-ND,,Yageo,,,RC0603FR-07130KL,,,130k
1,143k,R-EU_143KR0603,R0603,R22,"RESISTOR, European symbol",311-143KHRCT-ND,,Yageo,,,RC0603FR-07143KL,,,143k
2,180k,R-EU_180KR0402,R0402,"R65, R66","RESISTOR, European symbol",311-180KLRCT-ND,,Yageo,,,RC0402FR-07180KL,,,180k
4,180k,R-EU_180KR0603,R0603,"R1, R5, R7, R8","RESISTOR, European symbol",P180KHCT-ND,,Panasonic,,,ERJ-3EKF1803V,,,180k
1,182k,R-EU_182KR0603,R0603,R13,"RESISTOR, European symbol",P182KHCT-ND,,Panasonic,,,ERJ-3EKF1823V,,,182k
6,1M,R-EU_1MR0402,R0402,"R53, R55, R56, R59, R64, R68","RESISTOR, European symbol",311-1.00MLRCT-ND,,Yageo,,,RC0402FR-071ML,,,1M
1,1M,R-EU_1MR0603,R0603,R71,"RESISTOR, European symbol",P1.00MHCT-ND,,Panasonic,,,ERJ-3EKF1004V,,,1M
1,1k,R-EU_1KR0402,R0402,R12,"RESISTOR, European symbol",311-1.00KLRCT-ND,,Yageo,,,RC0402FR-071KL,,,1k
1,1uF,C-EU0.1UFC0402,C0402,C42,"CAPACITOR, European symbol",1276-6524-1-ND,,Samsung,,,CL10B105MO8NNWC,,,
2,1uF,C-EU1UFC0603,C0603,"C11, C13","CAPACITOR, European symbol",490-10479-1-ND,,Murata,,,GRM188R61C105KA12D,,,
1,1uH,INDUCTORLQS_3X3,WE-LQS(3X3),L3,Genaric inductor,732-5491-1-ND,,Wurth,,,74404032010,,,
1,20,R-EU_20R0402,R0402,R11,"RESISTOR, European symbol",311-20LRCT-ND,,Yageo,,,RC0402FR-0720RL,,,20
1,200k,R-EU_200KR0603,R0603,R70,"RESISTOR, European symbol",311-200KHRCT-ND,,Yageo,,,RC0603FR-07200KL,,,200k
1,20k,R-EU_20KR0603,R0603,R51,"RESISTOR, European symbol",311-20.0KHRCT-ND,,Yageo,,,RC0603FR-0720KL,,,20k
1,220uF,CTANT_EU2917,C2917,C5,Genaric Tantalum Capacitor,478-5408-1-ND,,AVX,,,TPSY227K010R0100,,,
7,22uF,C-EU22UFC0805,C0805,"C2, C7, C8, C9, C10, C19, C20","CAPACITOR, European symbol",490-9952-1-ND,,Murata,,,GRM219R61C226ME15L,,,
2,27,R-EU_27R0402,R0402,"R34, R35","RESISTOR, European symbol",YAG3086CT-ND,,Yageo,,,RC0402FR-0727RL,,,27
4,287R,R-EU_232R0402,R0402,"R26, R27, R28, R29","RESISTOR, European symbol",YAG3063CT-ND,,Yageo,,,RC0402FR-07232RL,,,232
4,287R,R-EU_453R0402,R0402,"R30, R31, R32, R33","RESISTOR, European symbol",YAG3165CT-ND,,Yageo,,,RC0402FR-07453RL,,,453
3,2N7002,MOSFET-NCH-2N7002PW,SOT323,"Q4, Q7, Q8",N-channel MOSFETs,2N7002W-FDICT-ND,,Diodes Incorporated,,,2N7002W-7-F,TRANS-11151,2N7002,
1,2k,R-EU_2KR0402,R0402,R15,"RESISTOR, European symbol",311-2KLRCT-ND,,Yageo,,,RC0402FR-072KL,,,2k
2,330,R-EU_330R0402,R0402,"R37, R39","RESISTOR, European symbol",311-330HRCT-ND,,Yageo,,,RC0603FR-07330RL,,,330
1,330,R-EU_330R0402,R0402,R9,"RESISTOR, European symbol",311-330LRCT-ND,,Yageo,,,RC0402FR-07330RL,,,330
6,330,R-EU_330R0402,R0402,"R36, R38, R40, R42, R43, R44","RESISTOR, European symbol",311-330LRCT-ND,,Yageo,,,RC0603FR-07330RL,,,330
1,10k,R-EU_10K0603,R0603,R48,"RESISTOR, European symbol",311-10.0KHRCT-ND,,Yageo,,,RC0603FR-0710KL,,,10k
2,330k,R-EU_330KR0603,R0603,"R17, R62","RESISTOR, European symbol",P330KHCT-ND,,Panasonic,,,ERJ-3EKF3303V,,,330k
1,360k,R-EU_360KR0603,R0603,R3,"RESISTOR, European symbol",311-360KHRCT-ND,,Yageo,,,RC0603FR-07360KL,,,360k
1,3m,R-EU_0.003R0805,R0805,R10,"RESISTOR, European symbol",RHM.003AJCT-ND,,Rohm,,,PMR10EZPFV3L00,,,
1,4.7uF,C-EU4.7UFC0805,C0805,C1,"CAPACITOR, European symbol",399-7415-1-ND,,Kemet,,,C0805C475K4RACTU,,,
1,4.7uH,INDUCTORMAIA_4.1X4.1,WE-MAIA(4.1X4.1),L4,Genaric inductor,732-11316-1-ND,,Wurth,,,78438356047,,,
1,470k,R-EU_470KR0603,R0603,R21,"RESISTOR, European symbol",311-470KGRCT-ND,,Yageo,,,RC0603JR-07470KL,,,470k
1,50m,R-EU_0.05R0805,R0805,R18,"RESISTOR, European symbol",P50LLCT-ND,,Panasonic,,,ERJ-L06KF50MV,,,
1,6.8uH,INDUCTOR1008,1008,L1,Genaric inductor,732-4849-1-ND,,Wurth,,,74438323068,,,
1,68pF,C-EU68PFC0402,C0402,C6,"CAPACITOR, European symbol",732-7474-1-ND,,Wurth,,,8.85012E+11,,,
1,820k,R-EU_820KR0603,R0603,R6,"RESISTOR, European symbol",311-820KGRCT-ND,,Yageo,,,RC0603JR-07820KL,,,820k
1,91k,R-EU_91KR0603,R0603,R16,"RESISTOR, European symbol",P91.0KHCT-ND,,Panasonic,,,ERJ-3EKF9102V,,,91k
2,ADS1115,ADS1115,VSSOP_10,"U32, U33",ADS1115 - Sigma Delta ADC,296-38849-1-ND,,TI,,,ADS1115IDGSR,,,
1,ATMEGA1284M,ATMEGA1284M,MLF44-TH,IC1,8-bit Microcontroller with 128K Bytes In-System Programmable Flash,ATMEGA1284P-MURCT-ND,,Atmel,,,ATMEGA1284P-MUR,,,
1,AVRISP-6,AVRISP-6,AVRISP,ISP1,AVR ISP HEADER,609-3234-ND,,Amphenol,,,67997-206HLF,,,
1,BAT54C,BAT54C,SOT23-3,D8,BAT54C,BAT54CLT1GOSCT-ND,,ON Semiconductor,BAT54CLT1G,,,,,
1,BATTERY_COIN12MM,BATTERY_COIN12MM,LINX_BAT-HLD-012-SMT,BT1,Coin Cell Battery Holder,BAT-HLD-012-SMT-ND,,Linx,,,BAT-HLD-012-SMT,,,
1,BME280,BME280,BME280,U31,BME280 - Combined Digital Humidity and Pressure Sensor,828-1063-1-ND,BME280,Bosch,,,BME280,,,
1,BQ2980RUG,BQ2980RUG,RUG_S-PQFP-N8,U5,"BQ2980 - Voltage, Current, Temperature Protectors with an Integrated High-Side NFET (BMS)",296-47578-1-ND,,TI,,595-BQ298000RUGT,BQ298000RUGT,,,
1,BUTTON2.6X1.6,BUTTON2.6X1.6,SWITCH_2.6X1.6,S5,Genaric SPST Pushbutton,P19888CT-ND,,Panasonic ,,,EVP-BB2A9B000,,,
2,BUTTON4.2X3.2,BUTTON4.2X3.2,SWITCH_4.2X3.2,"S3, S4",Genaric SPST Pushbutton,CKN10504CT-ND,,C&K,,,PTS810 SJG 250 SMTR LFS,,,
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
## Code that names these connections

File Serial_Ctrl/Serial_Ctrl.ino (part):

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boolean Debug = false; //FIX!!
char ReadArray[25] = {0};

const uint8_t C1 = 19; //Control pins for V_HP
const uint8_t C0 = 18;

const uint8_t EN_BUS_PRIME = 23;  //Power enable lines for buses
const uint8_t EN_BUS_SEC = 22;

const uint8_t GPIO[4] = {12, 25, 3, 26}; //GPIO pins 0~3, 0,1 on primary bus, 2,3 on secondary bus. 0 and 2 PWM capable

const uint8_t Global_Int = 28; //Global interrupt from IO Expander
const uint8_t Log_Int = 27; //Interrupt for logging event

////////////////////////////////////SD////////////////////////////////////////
const uint8_t SD_CS = 4; //Define chip select for SD card
char FileNameC[11]; //Used for file handling
boolean SD_Init = false;

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boolean TestSD()
{
  boolean SDError = false;
  pinMode(SD_CS, OUTPUT);
  SPI.setDataMode(SPI_MODE0);
  SPI.setClockDivider(SPI_CLOCK_DIV2); //Sts SPI clock to 4 MHz for an 8 MHz system clock

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
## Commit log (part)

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2018-10-18 Added Creative Commons Licence
2018-10-18 Added pin connections document
2018-10-23 Created schematic and board, beginning ECAD population
2018-10-25 Continued schematic additions, prelim part placement
2018-10-26 Preliminary power section layout
2018-10-27 Continued layout, board size change
2018-10-29 Continued layout, major of power and prime bus done
2018-10-30 Continued layout, majority of secondary bus, low power
2018-10-30 Added OR Controller simulation
    Also updated gitignore to prevent issues with LTSpice stuff
2018-10-30 Continued layout, starting on SD and Feather header
2018-11-01 Layout tentative completed, sent to DFM check
    Layout complete for v0.0, pending final triple check, sent to DFM check to verify manufacture issues. Ready for final external review.
2018-11-01 Added PDFs of prelim v0.0 schematic
2018-11-01 Added board PDFs of prelim v0.0
2018-11-02 Minor board edits, updated gerbers, pending DFM
2018-11-07 Updated BOM info
    Added info to schematic to support auto-generating BOM
2018-11-10 Added very early RockBlock breakout
2018-11-13 Preliminary layout of RockBlock Breakout
    Still needs cleanup and some verification
2018-11-13 Aligned buttons on RockBlock breakout
2018-11-15 Routing cleanup
2018-11-16 Created serial control demo
    Still need to develop serial control demo...
2018-11-19 Built Serial Ctrl script
    Flushed out serial ctrl test script to allow for pin by pin and sub module testing and control
2018-11-19 Updated inductor L2 layout
    Fixed size and part number of inductor to match XHMI layout
2018-11-20 First round of fixes to hardware
    changed SD card holder, power switches, power switch topology, add pull up resistors to IO expander, to allow for new non-internal pull up module, added some silkscreen, added 3v3 core I2C pullups
2018-11-20 Layout fixes
    Improvements and cleanup in the layout, should get final review before being sent out to fab
2018-11-26 Generated Gerbers, Minor Updates
    v0.1 Sent to fab
2018-11-29 Added dimensions, updated part numbers
2018-11-30 Fixed part value for TCA9555 (to TCA9535)
2019-01-09 Updated pin connections doc
2019-01-10 Fixed MPPT set resistors
    Fixed the order of the MPPT voltage set resistors. Correct values were used, but in the wrong orientation, this has been corrected
2019-01-19 Fixed message format in `Serial_Ctrl`
2019-02-07 Added 5v LP control test board
2019-02-08 Added 5v LP modified test board
2019-02-09 Initial schematic updated for v0.2
    First round of updates to schematic for v0.2 update, needs verification before layout begins
2019-02-12 Initial layout update for v0.2
    Layout mainly complete, review required, need to delete some extraneous parts
2019-02-12 Added gerbers for modified 5v test board
2019-02-12 Removed extraneous protection circuit
    Removed deprecated MOSFET protection circuit on ADC
2019-02-14 Updated test boards for VolteraV1
    Attempted to maximize compatibility with Voltera V1 system
2019-02-16 Updates to 5v test board
    Added additional converter to 5v test setup, also condensed all units onto a single board and generated gerbers for compatibility with Sunstone PCB
2019-02-20 Added updated gerbers for Sunstone fab
2019-03-14 Minor cleanup
    Top layer checked and verified, bottom layer still needs cleanup and verification, also update version number!
2019-03-16 Minor cleanup and gerber generation, ready for v0.2
2019-03-21 Improved paste layout, generated stencil gerbers
    Updated the paste distribution on several parts, generated gerbers for the stencil
2019-06-05 Remove I2C disable with power off
2019-06-06 Initial updates for v0.3
    Additional routing required, need to add ADC switch enable, need to add efficiency modification to mppt
2019-06-06 Layout updates, cleanup required, minor testing
2019-06-06 Continued layout, generated gerbers
    Improved layout, generated gerbers, final design review before send to fab
2019-07-31 Naming/part cleanup
2019-07-31 Added testing files for Boron and Resnik
    Added multiple testing files, omitted compiled binaries for Boron
2019-08-13 Hardware fixes, review and verification required, gerber generated
    Gerber generated and sent to DFM, verification and review required
2019-08-14 Silk screen edits, generated gerbers, v0.4 send to fab
2019-08-14 Minor value changes, generated BoM for quote generation
2019-08-22 Added Ref ID images, updated BoM for new parts, added pick and place
2019-11-02 Added reference designators, cleanup
2019-11-02 Added Boron test files
2020-02-13 Update to fix issue #6, start of v0.5
    Fixed battery parasitic draw into ADC issue be connecting ADC to battery through protection circuit, preventing the parasitic draw from discharging the battery below the UVLO voltage
2020-04-25 Remove old Gerber zips
2020-04-25 Current BoM only; no versions in file names
2020-04-25 5V_LP_Test board to subdirectory
2020-04-25 v0.0; old
2020-04-25 Old code for renumbering pins; keep in archive only
2020-04-30 Construction and user's guide, first draft
2020-04-30 Images for new documentation
2020-04-30 Battery mount and strap (primary AA)
2020-04-30 PolyCase P/N for fitting box
2020-04-30 CC BY-SA 4.0
2020-05-01 GPL for code
2020-05-03 Label all jumpers: text and diagrams
2020-05-07 Add solder wick to supplies list
2020-05-27 Materials: screws, power system
2020-05-27 Cable gland link (ElecDirect); formatting
2020-06-04 Adafruit plug for solar panel
2020-06-18 Sources of support
2020-06-18 Remove blank line between images
2020-06-18 USGS Innovation Center
2020-06-18 Fix USGS logo
2020-10-01 Updated fastener BOM and links
2020-10-02 Added Mounting Plate drawings
2020-10-02 Updated Materials list on Readme
    Added mounting plate link and changed Batteries to Power section, added link to AA battery pack
2020-10-02 Updated Resnik mounting screws
2020-10-03 Updated mounting plate drawings
    Updated mounting plate drawings to account for battery packs rotated 90 degrees, Resnik board centered.
2020-10-26 Added STEP file of Mounting Plate v1.3
2020-10-26 Rename Mounting Plate.step to Resnik Mounting Plate v1.3.step
2020-10-27 Mounting plate for milling: routing outside the lines in Easel should work
2020-11-01 Spaces --> Underscores in file names
2020-11-01 AA backup battery box (x3, 3D print files)
2020-11-01 Battery mount for small Margay box
2020-11-01 AA battery mount for 3D printing
2020-11-01 Update to Resnik large-box small-holder with countersunk screw holes
2021-03-02 DOI badge
2021-03-05 parallel --> series typo fix
2021-03-10 On-board I2C, SPI, and UART devices
2021-03-11 Polishing the Status Codes section a bit for consistency
2021-03-11 typo
2021-07-05 vim swapfiles
2021-07-05 Dimensioned drawings
2021-07-05 WQ57 mounting plate
2021-07-05 Resnik in WQ55 box: too small?
2021-07-05 Too small to be practical
2021-07-05 Organized for WH-16 and WQ-57 boxes
2021-07-05 3 years old: Deprecated
2021-07-05 v0.4/deprecated
2021-07-05 Moved to RockBLOCK-feather repo
2021-07-05 Okapi name change
2021-07-05 Manual merge
2021-07-05 Two more Resnik --> Okapi
2021-07-05 Add dimension lines
2021-07-05 Okapi naming
2021-07-05 Comment out libraries that are not in our standard bundle
2021-07-05 Use our MPC4725 library mod (NW interface)
2021-07-05 Updated for MCP23108; left deliberately incomplete (which port?)
2021-07-09 dev namesake: Judy Resnik
2021-07-18 "run" capitalization fix in example code
2021-07-19 ISP driver note
2021-07-22 punctuation consistency in field operator's guide
2021-08-08 note consistency changes
2021-08-08 note consistency changes pt. 2
2024-10-14 Updated layout
2024-10-14 Continued layout updates
2024-10-21 CSA layout
2024-10-30 Design updates toward v1.0
2024-10-31 Continued design updates
2024-11-02 v1.0 updates
2026-06-03 Large-box battery mount with strap: used in deployments.
2026-06-03 CAM files, unverified.

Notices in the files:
README.md:
This work is licensed under a Creative Commons Attribution-ShareAlike 4.0 International License.
